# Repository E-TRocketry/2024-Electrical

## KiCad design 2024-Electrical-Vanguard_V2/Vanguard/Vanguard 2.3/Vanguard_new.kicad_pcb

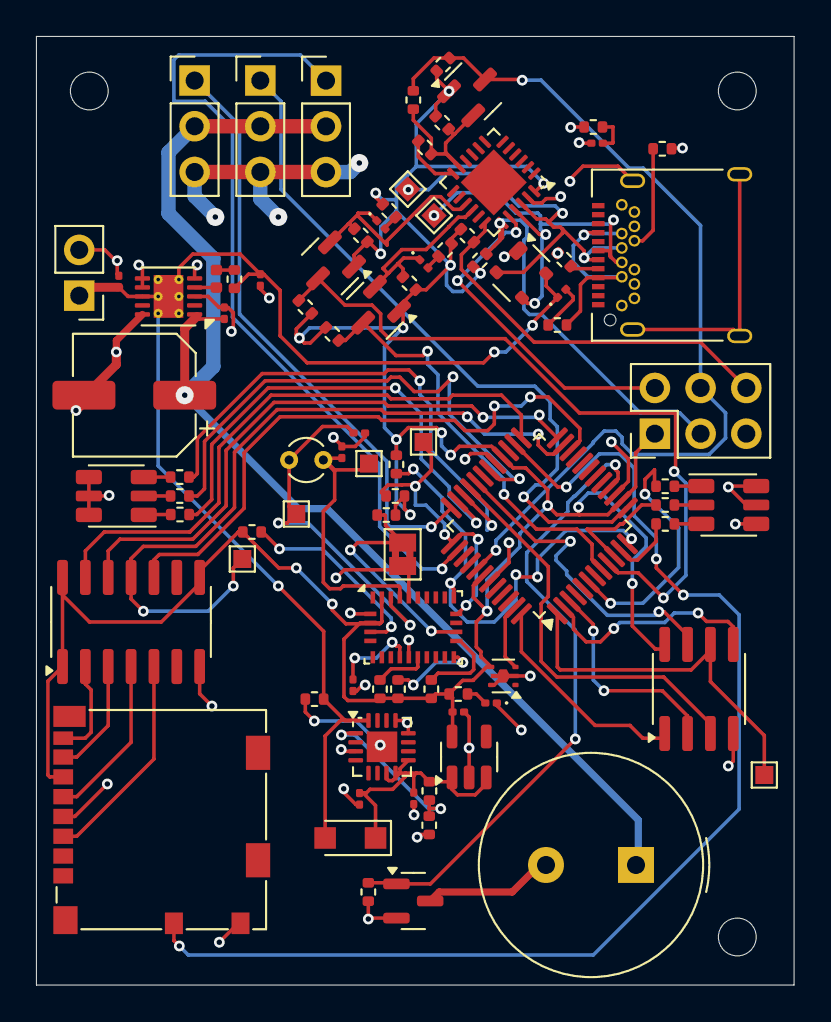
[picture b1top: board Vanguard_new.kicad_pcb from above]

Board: 4 copper layers, 42.1 x 52.7 mm, 85 parts (0 on the bottom side), 71 nets.

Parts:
ADR1: SolderJumper-2_P1.3mm_Bridged2Bar_Pad1.0x1.5mm
BZ1: Buzzer; Buzzer_TDK_PS1240P02BT_D12.2mm_H6.5mm
C1: 4n7; C_0201_0603Metric
C2, C3: 22p; C_0201_0603Metric
C4, C5: 22u; C_0201_0603Metric
C6, C11: 1u; C_0201_0603Metric
C7: 0u1; C_0201_0603Metric
C8: 10u; C_0201_0603Metric
C9: 2u2; C_0201_0603Metric
C10: 100u; CP_Elec_6.3x5.4
D1: PRTR5V0U2X; SOT-143
D2, D3, D7: LED; LED_0201_0603Metric
D5: GREEN; LED_0201_0603Metric
D6: PMEG6020ER; Nexperia_CFP3_SOD-123W
J1: USB_C_Receptacle_USB2.0_16P; USB_C_Receptacle_Amphenol_12401548E4-2A
J2: Conn_02x03_Pin; PinHeader_2x03_P2.54mm_Vertical
J3: Micro_SD_Card_Det1; microSD_HC_Molex_104031-0811
J4: STARBOARD_SERVO; PinHeader_1x03_P2.54mm_Vertical
J5: PORTSIDE_SERVO; PinHeader_1x03_P2.54mm_Vertical
J6: Battery In; PinHeader_1x02_P2.54mm_Vertical
J7: EJECTION_SERVO; PinHeader_1x03_P2.54mm_Vertical
L1: 6u8; L_0402_1005Metric
PORTSIDE_RGB1: SMLVN6RGB; LED_ROHM_SMLVN6
Q1, Q2, Q3, Q4: BSS138; SOT-23
R1: 1M; R_0402_1005Metric
R2, R6, R7, R9, R10, R11, R12, R13, R19, R20: 4k7; R_0402_1005Metric
R3, R4: 330; R_0402_1005Metric
R5: 0; R_0402_1005Metric
R8: DNP; R_0402_1005Metric
R14, R15: 100k; R_0402_1005Metric
R16: 19k1; R_0402_1005Metric
R17: 330R; R_0402_1005Metric
R18, R23, R24: 10k; R_0402_1005Metric
R21, R22, R34: 2k2; R_0402_1005Metric
R25, R26, R27, R28, R29, R30: 220; R_0402_1005Metric
R31, R32: 5k1; R_0402_1005Metric
R33: 5m; R_0402_1005Metric
R35: R220; R_0402_1005Metric
STARBOARD_RGB1: SMLVN6RGB; LED_ROHM_SMLVN6
TP1, TP2, TP3, TP4, TP5, TP6, TP7: TestPoint; TestPoint_Pad_1.0x1.0mm
U1: ATSAMD11D14A-M; QFN-24-1EP_4x4mm_P0.5mm_EP2.6x2.6mm
U2: ATmega4809-A; TQFP-48_7x7mm_P0.5mm
U3: AT25DF641A-SH-T; SOIC-8_3.9x4.9mm_P1.27mm
U4: AP2112K-3.3; SOT-23-5
U5: BD1020HFV; HVSOF5
U6: BNO086; LGA-28_5.2x3.8mm_P0.5mm
U7: TXB0104D; SOIC-14_3.9x8.7mm_P1.27mm
U8: TPS61092; DFN-10-1EP_3x3mm_P0.5mm_EP1.65x2.38mm_ThermalVias
U9: MPM3610AGQV-P; QFN-16-1EP_3x3mm_P0.5mm_EP1.7x1.7mm
Y1: 32.768kHz; Crystal_C26-LF_D2.1mm_L6.5mm_Vertical

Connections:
+3.3V: C6.1, J2.1, J3.6 (VSS), Q1.1 (G), Q2.1 (G), Q3.1 (G), R2.1, R3.1, R4.1, R6.1, R7.1, R9.1, R10.1, R11.1, R12.1, R13.1, R17.1, R18.2, R19.2, R20.2, R21.1, R22.1, R23.1, R24.1, U1.24 (VDD), U2.14 (VCC), U2.28 (AVCC), U2.42 (VCC), U3.8 (VCC), U4.5 (VOUT), U5.4 (VDD), U6.3 (VDD), U6.28 (VDDIO), U7.1 (VCCA), U7.8 (OE), U7.14 (VCCB)
+5V: BZ1.1 (+), C9.1, C10.1, J4.2, J5.2, J7.2, U8.1 (VOUT)
/RX_UPDI: R5.1, U1.12 (PA15)
/TX_UPDI: Q1.2 (S), R5.2, R6.2, R8.1, U1.11 (PA14)
BATT_IN: C4.1, C8.1, D1.4 (VCC), D6.2 (A), D7.1 (K), J6.1, R14.1, R33.2, U8.8 (VBAT), U8.11 (EN), U9.16 (IN)
BUZZER: Q4.1 (G), R34.1, U2.16 (PC4)
CD: J3.9 (DET), U2.26 (PD6)
D4: TP3.1, U2.23 (PD3), U7.11 (B3)
D5: U2.22 (PD2), U7.10 (B4)
D6: U2.24 (PD4), U7.12 (B2)
D7: U2.25 (PD5), U7.13 (B1)
EJEC_SERVO: J7.1, U2.38 (PF4)
GND: ADR1.1 (A), C1.1, C1.2, C2.2, C3.2, C4.2, C5.2, C6.2, C7.2, C8.2, C9.2, C10.2, C11.2, D1.1 (GND), D5.1 (K), J1.A1 (GND), J1.A12 (GND), J1.B1 (GND), J1.B12 (GND), J1.S1 (SHIELD), J2.5, J3.4 (VDD), J3.10 (SHIELD), J4.3, J5.3, J6.2, J7.3, PORTSIDE_RGB1.4 (GK), PORTSIDE_RGB1.5 (RK), PORTSIDE_RGB1.6 (BK), Q4.2 (S), R1.1, R1.2, R16.2, R31.2, R32.2, R34.2, STARBOARD_RGB1.4 (GK), STARBOARD_RGB1.5 (RK), STARBOARD_RGB1.6 (BK), U1.23 (GND), U2.15 (GND), U2.29 (GND), U2.43 (GND), U3.4 (GND), U4.2 (GND), U5.2 (PG), U5.5 (GND), U6.2 (GND), U6.10 (CLKSEL0), U6.25 (GNDIO), U7.7 (GND), U8.3 (SW), U8.5 (PGND), U8.6 (PGND), U8.7 (PGND), U8.10 (SYNC), U9.3 (AGND), U9.12 (PGND), U9.13 (PGND), U9.14 (PGND)
HOLD: U2.32 (PE2), U3.7 (~HOLD)
unnamed: ADR1.2 (B), R23.2, U6.17 (SA0/H_MOSI)
unnamed: BZ1.2 (-), Q4.3 (D)
unnamed: D1.2 (I/O1), J1.A6 (D+), J1.B6 (D+), TP1.1, U1.22 (PA25)
unnamed: D1.3 (I/O2), J1.A7 (D-), J1.B7 (D-), TP2.1, U1.21 (PA24)
unnamed: D2.2 (A), R4.2
unnamed: D2.1 (K), Q3.2 (S), R9.2, U1.15 (PA22)
unnamed: D3.2 (A), R3.2
unnamed: D3.1 (K), Q2.2 (S), R10.2, U1.16 (PA23)
unnamed: D5.2 (A), R17.2
unnamed: C5.1, C11.1, D6.1 (K), R15.1, U4.1 (VIN), U4.3 (EN), U9.7 (OUT), U9.8 (OUT), U9.9 (OUT)
unnamed: D7.2 (A), R35.1
unnamed: J1.A5 (CC1), R31.1
unnamed: J1.B5 (CC2), R32.1
unnamed: J1.A4 (VBUS), J1.A9 (VBUS), J1.B4 (VBUS), J1.B9 (VBUS), R35.2
unnamed: J2.2, U1.20 (PA31/SWDIO)
unnamed: J2.3, R2.2, U1.19 (PA30/SWCLK)
unnamed: J2.6, R11.2, U1.18 (PA28/~RST)
unnamed: J3.5 (CLK), U7.4 (A3)
unnamed: J3.3 (CMD), U7.5 (A4)
unnamed: J3.7 (DAT0), U7.3 (A2)
unnamed: J3.8 (DAT1), U7.2 (A1)
unnamed: L1.1, R33.1
unnamed: L1.2, U8.4 (SW)
unnamed: PORTSIDE_RGB1.1 (BA), R28.1
unnamed: PORTSIDE_RGB1.3 (GA), R30.1
unnamed: PORTSIDE_RGB1.2 (RA), R29.1
unnamed: R25.2, STARBOARD_RGB1.1 (BA)
unnamed: R27.2, STARBOARD_RGB1.3 (GA)
unnamed: R26.2, STARBOARD_RGB1.2 (RA)
unnamed: C7.1, U6.9 (CAP)
unnamed: R19.1, U6.15 (ENV_SCL)
unnamed: R20.1, U6.16 (ENV_SDA)
unnamed: C3.1, TP5.1, U6.27 (XIN32), Y1.2
unnamed: C2.1, TP6.1, U6.26 (XOUT32/CLKSEL1), Y1.1
unnamed: R24.2, U6.4 (~BOOT)
unnamed: R18.1, U6.11 (~RST)
unnamed: R14.2, U9.17 (EN)
unnamed: R15.2, R16.1, U9.1 (FB)
PA0/MISO: U2.3 (PA7), U3.2 (SO(SOI))
PA1/MOSI: U2.2 (PA6), U3.5 (SI(SIO))
PA2/SCK: TP4.1, U2.1 (PA5), U3.6 (SCK)
PA3/SS: U2.48 (PA4), U3.1 (~CS)
PORT_BLUE: R28.2, U2.35 (PF1)
PORT_GREEN: R30.2, U2.34 (PF0)
PORT_RED: R29.2, U2.30 (PE0)
PORT_SERVO: J5.1, U2.13 (PC3)
RX0: Q3.3 (D), R12.2, U2.9 (PB5)
SCL: R22.2, TP7.1, U2.37 (PF3), U6.19 (H_SCL/SCK/RX)
SDA: R21.2, U2.12 (PC2), U6.20 (H_SDA/H_MISO/TX)
STAR_BLUE: R25.1, U2.6 (PB2)
STAR_GREEN: R27.1, U2.11 (PC1)
STAR_RED: R26.1, U2.10 (PC0)
STAR_SERVO: J4.1, U2.36 (PF2)
TEMP_SENSOR: U2.47 (PA3), U5.3 (OUT)
TX0: Q2.3 (D), R13.2, U2.8 (PB4)
UPDI: J2.4, Q1.3 (D), R7.2, R8.2, U2.41 (UPDI)
WP: U2.33 (PE3), U3.3 (~WP)

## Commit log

2024-10-15 changed environment
2024-10-15 test initial
2024-12-30 added files
2024-12-30 some changes in the schematic
2024-12-30 wierd. add changes in v2 sch. power stabilization.
2024-12-30 closed KiCad
2024-12-31 fixed the errors in v2.3
2024-12-31 fixed a small battery error
2025-01-05 slight corrections in the input usb wiring
2025-01-16 testCommit
    ----
